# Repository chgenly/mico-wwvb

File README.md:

# &mu;WWVB: a tiny wwvb station

&mu;WWVB is a low power 60 khz [WWVB] transmitter used
to automatically set the time on radio synchronized clocks and wristwatches where the regular [WWVB] signal isn’t available. The system acquires
the correct time via GPS.

If you are interested in building a WWVB transmitter, I recommend you look at [pico wwvb](https://github.com/chgenly/pico-wwwvb).  It's much cheaper to build, and a lot less work.

## Anish Athalye's project

I started with this 2016 github project.

-  His github project https://github.com/anishathalye/micro-wwvb.git 
-  His [blog post][micro-wwvb-post].

Thanks to Anish for making it available. 

## My situation

I live in Forest Grove, Oregon.  The opposite coast where Anish had his problem. I'm not able to reliably receive [WWVB], and especially not inside my house.  

I started searching for information on WWVB signals and ran 
across Anish's project.  It was perfect for what I wanted to do.

Anish seemed to have access to a lot of equipment for building the physical part of the stand.    I don't have access so I'm just going to be using a simple plastic box as a case.

I haven't made my own PC board since 1974.  A lot of taping was involved and then an etching bath.  I was pleased to discover open source schematic and printed circuit board editors.  I was
also pleased to discover online services which would accept design files, either as [gerber files](https://en.wikipedia.org/wiki/Gerber_format) or kicad pcb files, and mail you a finished PCB.

## KiCad

For my open source schematic/PCB editor I chose [KiCad].  I had never used it before.  So there was a bit of a learning curve.

### autorouting
Install the Freerouting plugin.
1. Open KiCad Project Manager
1. Click on Plugin and Content Manager
1. Find Freerouting
1. Click on install
1. Click on Apply Pending Changes.
1. You will have to have Java installed for it to work.

## PCB fabrication service

I used [Osh Park](https://oshpark.com) as my fabrication service.  They accept KiCad pcb files directly.  No need to export to gerber files.  The are the cheapest service I could fine.  Interestingly, they just happen to be local to me.

[WWVB]: https://www.nist.gov/pml/time-and-frequency-division/radio-stations/wwvb
[micro-wwvb-post]: https://www.anishathalye.com/2016/12/26/micro-wwvb/

[KiCad]: https://www.kicad.org/

## ATTiny44a-SSUR

AVR family of processors.  8 bit risc architecture.

14 pin Dual inline package
Surfuce mount device

Just notes an decoding the suffix.

- 4KiB flash
- SS - 14S1 package
- U - Matte tin
- R - Tape and real
- 14S1 - 14-lead, 3.90 mm Narrow Body, Plastic Small Outline Package (SOIC)

## WWVB signal

WWVB transmit on 60 khz for atomic watches and clocks. One bit of data is sent once every second.
60 seconds are required to send all the bits for the time.
- 0: Power reduced for .2 seconds.
- 1: Power reduced for .5 seconds.
- mark: Power reduced for .8 seconds.

## Software

The top level software

1. Initialize pins for LEDs,  GPS serial communication and for the antenna. 
1. Loop
   1. Acquire time from GPS module
   1. Send the 1 minute WWVB signal ten times.

The 60 khz signal is generated using the ATTiny's 16 bit counter, and associated wave form generator.
The pulse width modulation output, PA5 (pin 8), is used to generate the 60khz signal.
The software divides a second into two parts.  The first part is the reduced power signal.  Reduced power in our case means no signal is sent.  The second part is full power signal.  Here pulse width modulation is set to 50% duty cycle.

Actually, a 20 khz signal is generated.  We depend on the third harmonic.  Apparently Anish found this more effective.

Timing for the signal is accomplished using a library routine to delay a certain number of milliseconds. I believe the millisecond
delay is trasformed to a cycle count delay.

During the full power signal, the blue led is turned on. The led is connected to PA7 (pin 6).

| Source file | Description |
|-------------|-------------|
| microwwvb.c | Top level.  init, get time, transmit time.|
| gps.c       | Send and receive GPS module commands.     |
| hardware.h  | Constants for LEDs, serial port           |
| serial.c    | Send and receive ascii data. |
| led.c       | Show status on LEDs                       |

## Programming

For a description of using an arduino to program the micro-wwvb board see:

https://docs.arduino.cc/built-in-examples/arduino-isp/ArduinoISP

Here are the steps to use the arduino to program the micro-wwvb board.

1. Wire the Arduino to the micro-wwvb.
1. Program the Arduino as ISP.
1. Test program to make blue and green leds flash.
1. Update src/makefile
1. Program micro-wwvb

### Wire Arduino to the micro-wwvb

micro-wwwvb pin header, as seen when the usb connector is on the left.
<pre>
| miso  | vcc  |
| sck   | mosi |
| reset | gnd  |
</pre>

You'll need six male to female cables.

- miso - arduino 12
- sck - adruino 13
- reset - arduino 10
- vcc - arduino 5v
- mosi - arduino 11
- gnd - arduino gnd

Make sure to disconnnect the ferrite loop antenna during programming.

### Program the Arduino as ISP

- Connect Arduino uno to your laptop
- Start adrduino ide
- Select board: arduino uno
- Select comm: comm3 (for me)
- File / Examples/ Arduino ISP /ArduinoISP
- Sketch / Upload

## Test program to make blue and green leds flash

- File / Preferences
  - Select Show verbose output during compile and upload.
- Use the following sketch
- Select board: attiny44
- Select comm: com3 (for me)
  - You can use the windows device manager to help you find
    the com.  Look under Ports.
- Tools / Programmer / arduino as ISP
- Sketch / Upload using programmer

```c
// Flash blue and green LEDS.  Blue is on when green is off.
void setup() {
  pinMode(PA1, OUTPUT);
  pinMode(PA7, OUTPUT);
}

void loop() {
  digitalWrite(PA1, HIGH); 
  digitalWrite(PA7, LOW); 
  delay(100);
  digitalWrite(PA1, LOW);
  digitalWrite(PA7, HIGH);
  delay(100);
```

### Update src/makefile

The reason you turned on verbose mode in the previous step
was so you could see paths to various tools.  Look in the output window and look for the path to avr-gcc, avrdude, and avrdude-conf.
Then set the variables at the top of src/Makefile.

| Variable | Comment|
|----------|------------------------------------------------------|
| GBIN     | Should point to the directory containing avr-gcc.exe |
| DCONF    | Should point to avrdude.conf                         |
| DBIN     | Should be the directory containing avrdude.exe       

### Program micro-wwvb

Goto the src directory and run make.  I used cygwin make.

- make program-fuses
- make program

## LEDs

The LEDS will indicated status

| Time | LED states |
|------|-----|
| Program startup / top of loop                                          | Green and blue flash three times |
| Waiting for start bit from GPS modules                                 | Green  |
| Searching for the '$' at the start of the response from the GPS module | Blue |
| Complete time response received from GPS module                             | Green on |
| Failure to receive expected response from GPS module                   | Green blinks twice, then blue blinks twice. |
| While transmitting WWVB signal                                         | Blue on for powered portion of the signal |

After startup, if the green and blue lights are stuck on,
you are not receiving anything from the GPS module.

After startup, if only the blue light is stuck on, 
you are receiving something from the GPS module, but the Initial '$' isn't being received.

If everything is working, you should see the Green light go solid, and the blue light flash
slowly with wwvb time data.

## Mechanical

To mount the gps module, which has no screw holes, I used a strap cut from a Fiji water bottle.  The Fiji bottle was rectangular, so I could cut out 
a relatively flat piece of plastic.  I created a template
in Gimp (image editor) and used a sharp craft knife to cut the plastic.

Here's the strap:

You can see how the central hole is sized for the GPS module.

I'll drill small holes in the tabs for screws.

I used a plastic food container as the case for the project.

## Changes

### Board
My first attempt at the board was incorrect.  I got the order of the pins on the GPS connector backwards.  I didn't
realize the cable that came with the GPS module was a reversing cable.  I fixed this for my
purposes by using a non-reversing cable.  

I have updated the KiCAD files to fix the pin ordering problem.   The images of the schematic and
the board have been updated too.  However, I'v never had these boards manufactured, and so never 
tested the latest board design.  I don't expect you will have problems, but if you do, you can start looking there.

### GPS module

The original GPS modules was the EM-506.  Due to the pin ordering problem, I
burned out the GPS module.  When I went to reorder it, it wasn't available.
It had been changed to the EM-506N5.  They are largely compatible.  However
the module is no longer initialized using $PSRF commands, instead a
proprietary command, $PAIR, is used.  The software and the bill of materials
has been updated to reflect the new module.

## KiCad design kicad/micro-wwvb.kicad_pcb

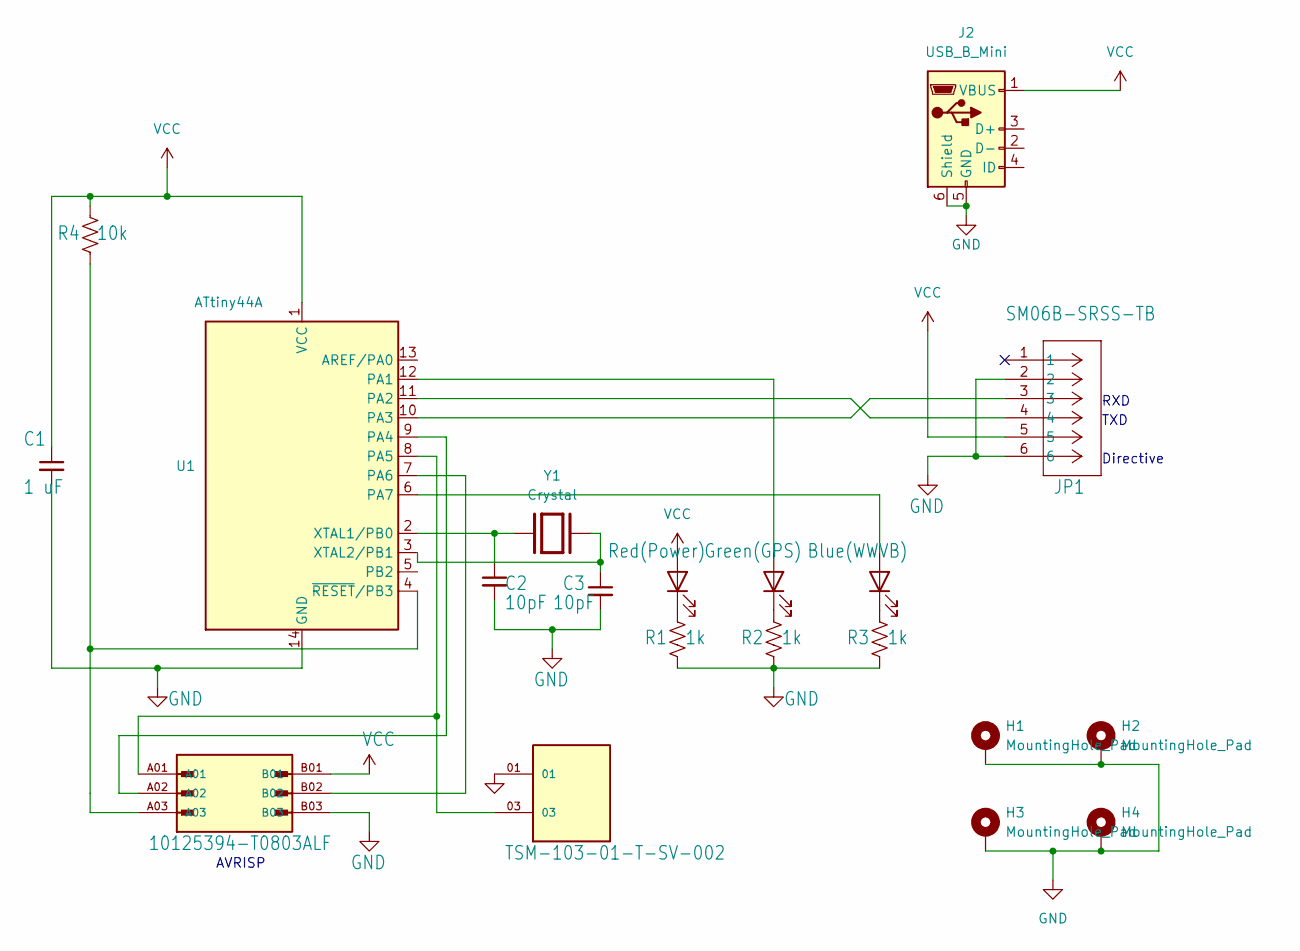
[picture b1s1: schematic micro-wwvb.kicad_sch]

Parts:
C1: 1 uF; C_1206_3216Metric_Pad1.33x1.80mm_HandSolder
C2, C3: 10pF; C_1206_3216Metric_Pad1.33x1.80mm_HandSolder
H1, H2, H3, H4: MountingHole_Pad; MountingHole_3.5mm_Pad
J2: USB_B_Mini; USB_Mini-B_Wuerth_65100516121_Horizontal
JP1: SM06B-SRSS-TB; CONN_SM06B-SRSS-TB_JST
LED1: Red(Power); LED_1206_3216Metric
LED2: Green(GPS); LED_1206_3216Metric
LED3: Blue(WWVB); LED_1206_3216Metric
R1, R2, R3: 1k; R_1206_3216Metric_Pad1.30x1.75mm_HandSolder
R4: 10k; R_1206_3216Metric_Pad1.30x1.75mm_HandSolder
U1: ATtiny44A; 14S1_ATM-M
U$1: TSM-103-01-T-SV-002; SAMTEC_TSM-103-01-T-SV-002
U$2: 10125394-T0803ALF; AMPHENOL_10125394-T0803ALF; PARTREV B
Y1: Crystal; XTAL_ABM3-20.000MHZ-B2-T; part number ABM3-20.000MHZ-B2-T

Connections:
GND: C1.2, C2.2, C3.2, H1.1, H2.1, H3.1, H4.1, J2.5 (GND), J2.6 (Shield), JP1.2, JP1.6, R1.1, R2.1, R3.1, U1.14 (GND), U$1.01, U$2.B03
unnamed: LED1.1 (K), R1.2
unnamed: LED2.2 (A), U1.12 (PA1)
unnamed: LED2.1 (K), R2.2
unnamed: LED3.2 (A), U1.6 (PA7)
unnamed: LED3.1 (K), R3.2
unnamed: JP1.4, U1.11 (PA2)
unnamed: JP1.3, U1.10 (PA3)
unnamed: U1.9 (PA4), U$2.A02
unnamed: U1.8 (PA5), U$1.03, U$2.A01
unnamed: U1.7 (PA6), U$2.B02
unnamed: C2.1, U1.2 (XTAL1/PB0), Y1.1
unnamed: C3.1, U1.3 (XTAL2/PB1), Y1.2
unnamed: R4.1, U1.4 (~RESET/PB3), U$2.A03
VCC: C1.1, J2.1 (VBUS), JP1.5, LED1.2 (A), R4.2, U1.1 (VCC), U$2.B01

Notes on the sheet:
TXD
RXD
AVRISP
Directive

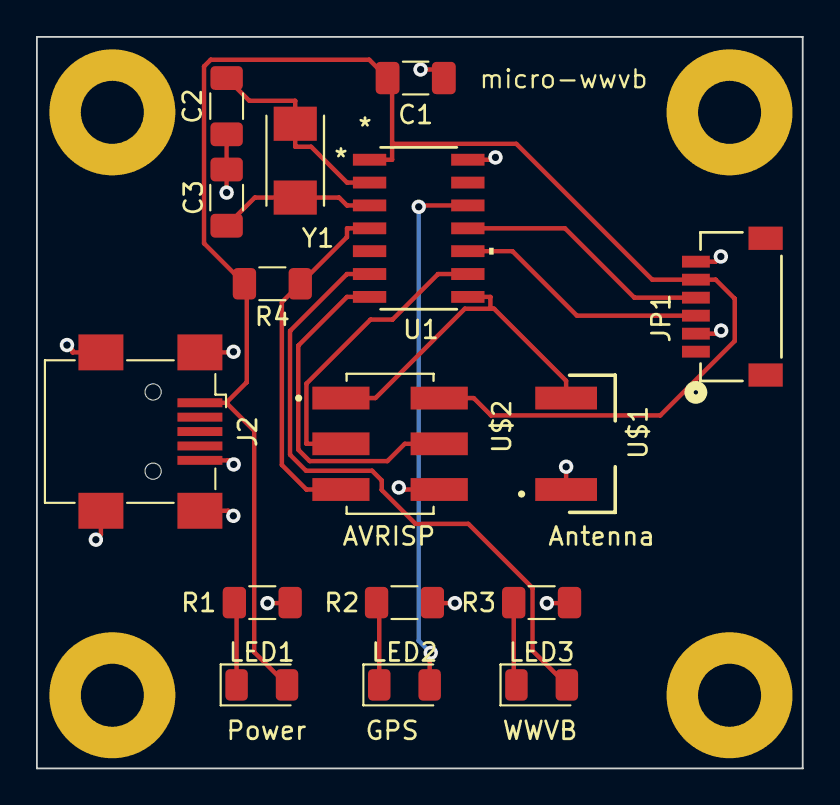
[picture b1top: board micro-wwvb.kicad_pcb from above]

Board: 2 copper layers, 42.5 x 40.6 mm, 20 parts (0 on the bottom side), 15 nets.

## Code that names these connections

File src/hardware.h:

#ifndef HARDWARE_H
#define HARDWARE_H

#include "serial.h"
#include <avr/io.h>

#define GPS_BAUD_RATE BAUD_RATE_4800
#define GPS_PORT PORTA
#define GPS_PORT_DDR DDRA
#define GPS_PORT_NUM PA3
#define GPS_PIN PINA
#define GPS_PIN_DDR DDRA
#define GPS_PIN_NUM PA2

#define LED_G_PORT PORTA
#define LED_G_PORT_DDR DDRA
#define LED_G_PORT_NUM PA1
#define LED_B_PORT PORTA
#define LED_B_PORT_DDR DDRA
#define LED_B_PORT_NUM PA7

#endif // HARDWARE_H

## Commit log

2023-10-27 Initial checkin
2023-10-27 Add fabrication service to README.md.
2023-10-27 Added silkscreen text to the back. Updated README.md with ATTiny info.
2023-10-27 Added ATTiny data sheet.
2023-10-27 Added image directory. Updated README.md to use images.
2023-10-28 Working on the bom
2023-10-28 More bom changes. Sparkfun want to charge $30 for shipping. So i moved away from them.
2023-10-28 Updated BOM to what was actually ordered. Add 3 pin hdr library for antenna. Although I'm not using this on the board I ordered. If I spin it again, I'll use this.
2023-10-28 Started a section in the README to describe what the software is doing.
2023-11-03 More for README.md
2023-11-14 LEDs show more status. Updated README.md.
2024-02-28 SEND_TEST: If defined in microwwvb.c the GPS module will be ignored and a fixed time will be sent.
2024-03-05 Yikes! I reversed all the pins on the gps connector.
    I didn't realize the plug had to be turned
    upside down to fit it into the connector.
    The kicad files have been updated. It also seems
    I've swapped the transmit and receive on the gps
    connector. I've updated the code to compensate.
    Found compatibility problems when using a windows
2024-03-05 Clarified LED states.
2024-03-05 Added workspace file
2024-03-05 Updated the images for the schematic and board with gps pin order corrected.
2024-03-05 Added led_debug() to help debugging. Calls are dropped into the code at various points to see if they are reached. Production code should not call this.
2024-03-06 The new GPS module does not support $PSRF commands.
    The EM506 supports $PSRF for initialization. The EM506N5 uses the $PAIR command for initialization.
2024-03-08 Updated REAME.md with pointer to pico-wwvb, changed how leds indicate an error.
2024-03-10 Sometimes the GPS module doesn't respond to initialization commands. I added a one second delay before initializing the module.
2024-03-15 Added pictures and a description for the GPS strap.
2024-03-19 Add picture of micro wwvb in a case.
